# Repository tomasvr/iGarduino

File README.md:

<h1>Introduction</h1>

The iGarduino is a simple, budget-friendly device which measures the moisture level in soil and waters your plants whenever necessary.

The ESP8266-12E functions as the brain of the device and allows you to establish a Wifi connection for data plotting.

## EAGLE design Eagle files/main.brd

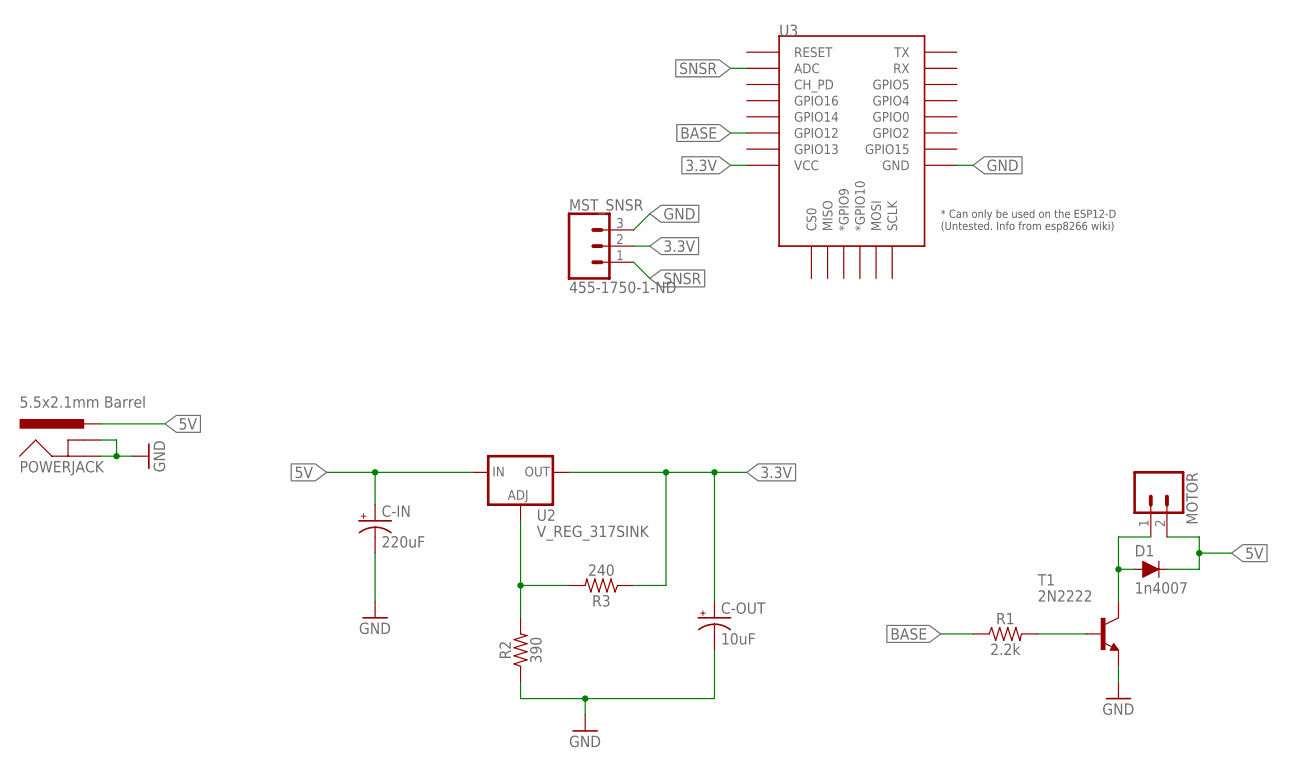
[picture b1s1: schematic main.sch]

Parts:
C-IN: 220uF; CPOL-RADIAL-2.5MM-5MM
C-OUT: 10uF; CPOL-RADIAL-2.5MM-5MM
D1: 1n4007; DIODE-1N4148
MOTOR: CONN_02; 1X02
MST_SNSR: 455-1750-1-ND; 1X03
POWERJACK: 5.5x2.1mm Barrel; POWER_JACK_SMD
R1: 2.2k; 0805
R2: 390; 0805
R3: 240; 0805
T1: 2N2222; TO92-EBC-OVAL
U2: V_REG_317SINK; TO220-ADJ
U3: ESP12ESMD; ESP12E-SMD

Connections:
3.3V: C-OUT.1 (+), MST_SNSR.2, R3.1, U2.OUT, U3.VCC
5V: C-IN.1 (+), D1.C, MOTOR.2, POWERJACK.VIN0 (PWR), U2.IN
BASE: R1.1, U3.GPIO12
GND: C-IN.2 (-), C-OUT.2 (-), MST_SNSR.3, POWERJACK.GND (GNDBREAK), POWERJACK.P$4 (GND), R2.1, T1.E, U3.GND
unnamed: R2.2, R3.2, U2.ADJ
unnamed: R1.2, T1.B
unnamed: D1.A, MOTOR.1, T1.C
SNSR: MST_SNSR.1, U3.ADC

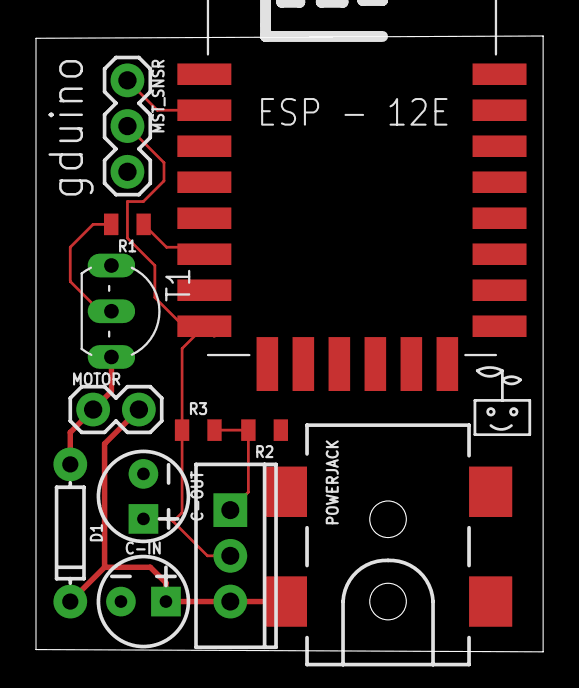
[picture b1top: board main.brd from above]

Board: 2 copper layers, 28.2 x 34.2 mm, 12 parts (0 on the bottom side), 8 nets.

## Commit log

2018-11-04 second commit
2018-11-04 added schematic and board file
2018-11-04 renamed ino file
2018-11-04 added eagle folder
2018-11-04 added pro. file
2018-11-04 added images
2018-11-05 made some small improvement to board routing

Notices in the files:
parts and their libraries:
SparkFun-Connectors: Licensing: Creative Commons ShareAlike 4.0 International - https://creativecommons.org/licenses/by-sa/4.0
